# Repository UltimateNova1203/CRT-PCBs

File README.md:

# CRT-PCBs
Custom PCBs for CRT TVs

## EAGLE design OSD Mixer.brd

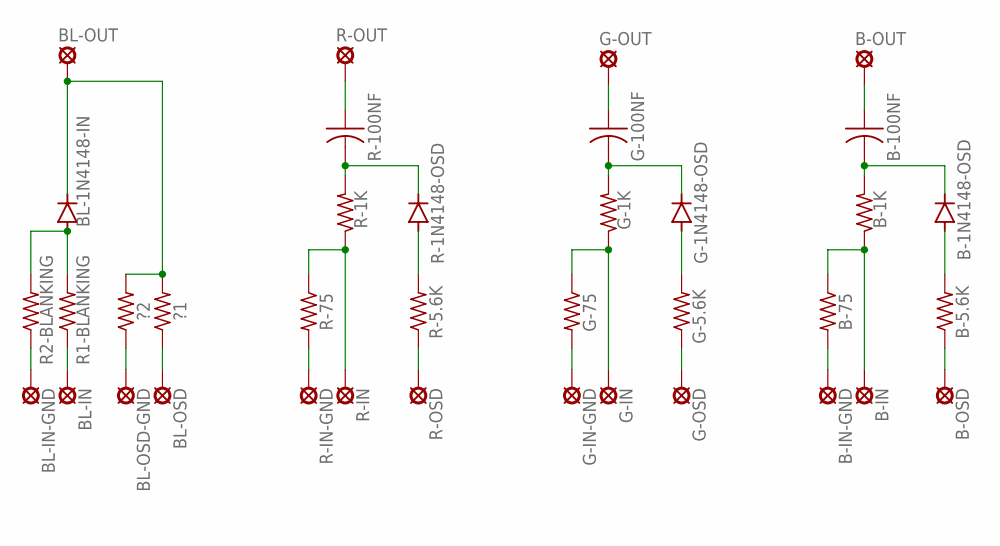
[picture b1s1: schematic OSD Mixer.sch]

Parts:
?1, ?2: R-US_0204/2V; 0204V
B-1K, B-5.6K, B-75: R-US_0204/2V; 0204V
B-1N4148-OSD: 1N4148DO35-7; DO35-7
B-100NF: C-US025-024X044; C025-024X044
B-IN: SE14
B-IN-GND: SE14
B-OSD: SE14
B-OUT: SE14
BL-1N4148-IN: 1N4148DO35-7; DO35-7
BL-IN: SE14
BL-IN-GND: SE14
BL-OSD: SE14
BL-OSD-GND: SE14
BL-OUT: SE14
G-1K, G-5.6K, G-75: R-US_0204/2V; 0204V
G-1N4148-OSD: 1N4148DO35-7; DO35-7
G-100NF: C-US025-024X044; C025-024X044
G-IN: SE14
G-IN-GND: SE14
G-OSD: SE14
G-OUT: SE14
R1-BLANKING, R2-BLANKING: R-US_0204/2V; 0204V
R-1K, R-5.6K, R-75: R-US_0204/2V; 0204V
R-1N4148-OSD: 1N4148DO35-7; DO35-7
R-100NF: C-US025-024X044; C025-024X044
R-IN: SE14
R-IN-GND: SE14
R-OSD: SE14
R-OUT: SE14

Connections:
unnamed: G-100NF.1, G-OUT.MP
unnamed: BL-IN-GND.MP, R2-BLANKING.1
unnamed: G-1K.2, G-1N4148-OSD.C, G-100NF.2
unnamed: G-75.2, G-IN-GND.MP
unnamed: G-1K.1, G-75.1, G-IN.MP
unnamed: G-5.6K.1, G-OSD.MP
unnamed: G-1N4148-OSD.A, G-5.6K.2
unnamed: R-100NF.1, R-OUT.MP
unnamed: R-75.2, R-IN-GND.MP
unnamed: BL-IN.MP, R1-BLANKING.1
unnamed: ?2.1, BL-OSD-GND.MP
unnamed: ?1.1, BL-OSD.MP
unnamed: R-1K.1, R-75.1, R-IN.MP
unnamed: R-5.6K.1, R-OSD.MP
unnamed: R-1N4148-OSD.A, R-5.6K.2
unnamed: BL-1N4148-IN.A, R1-BLANKING.2, R2-BLANKING.2
unnamed: B-75.2, B-IN-GND.MP
unnamed: B-1K.1, B-75.1, B-IN.MP
unnamed: B-5.6K.1, B-OSD.MP
unnamed: ?1.2, ?2.2, BL-1N4148-IN.C, BL-OUT.MP
unnamed: B-1N4148-OSD.A, B-5.6K.2
unnamed: B-1K.2, B-1N4148-OSD.C, B-100NF.2
unnamed: B-100NF.1, B-OUT.MP
unnamed: R-1K.2, R-1N4148-OSD.C, R-100NF.2

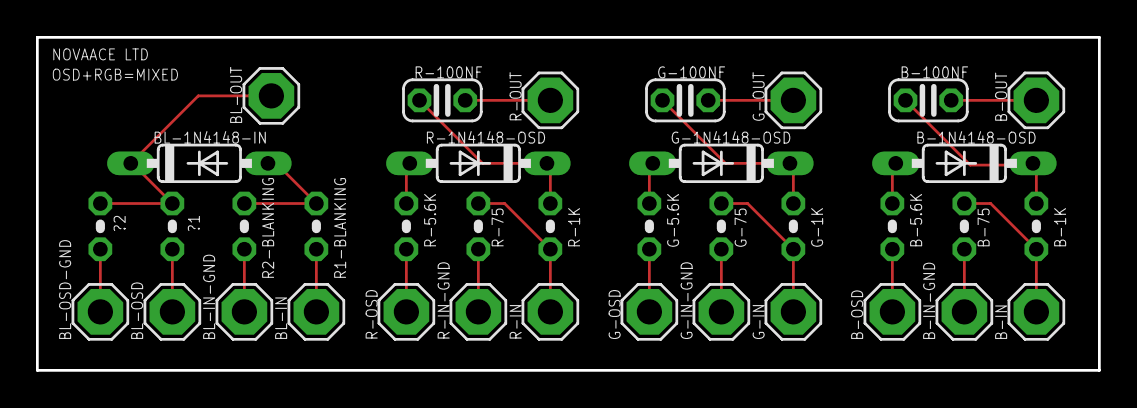
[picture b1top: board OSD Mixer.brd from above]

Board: 2 copper layers, 59.0 x 18.5 mm, 37 parts (0 on the bottom side), 24 nets.

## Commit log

2020-08-19 OSD+RGB=MIXED v1
